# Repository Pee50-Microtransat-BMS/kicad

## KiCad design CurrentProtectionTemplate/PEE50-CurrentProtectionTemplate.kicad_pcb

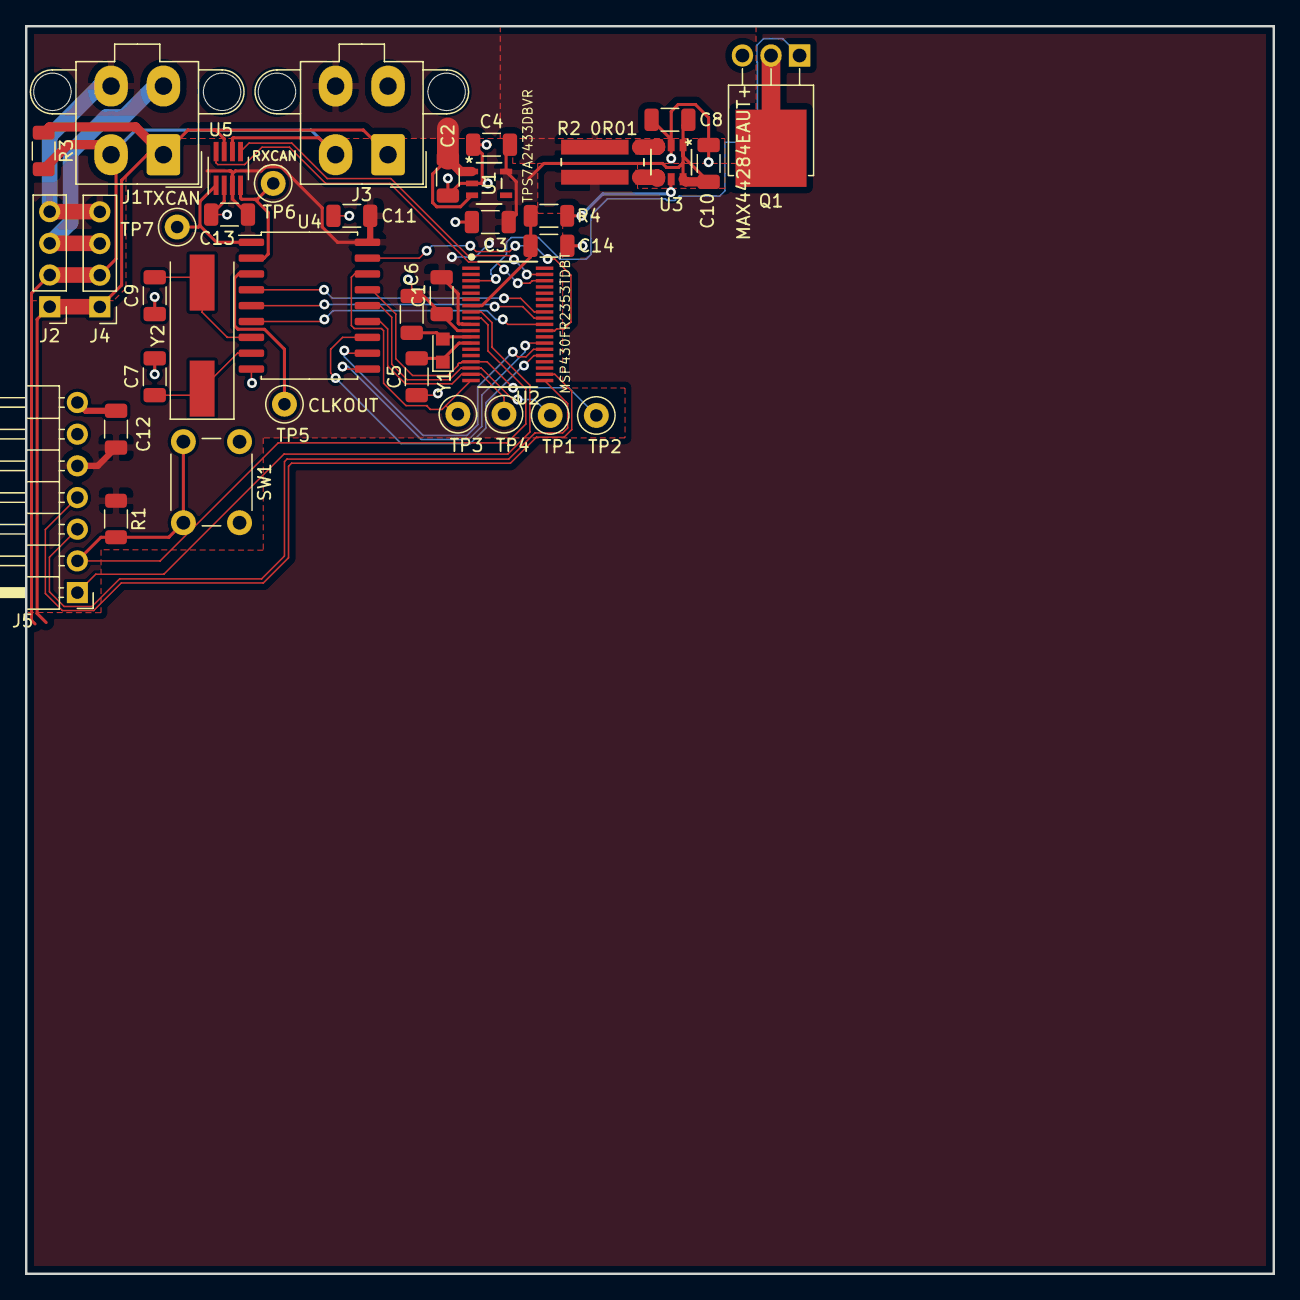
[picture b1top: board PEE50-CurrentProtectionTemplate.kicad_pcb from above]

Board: 2 copper layers, 100.0 x 100.0 mm, 39 parts (0 on the bottom side), 35 nets.

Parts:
C1, C4, C8, C11, C12, C13: 100nF; C_1206_3216Metric
C2: 1uF; C_1206_3216Metric
C3, C10: 4.7uF; C_1206_3216Metric
C5, C6: 12pF; C_1206_3216Metric
C7, C9: 18pF; C_1206_3216Metric
C14: 22nF; C_1206_3216Metric
J1: CAN_IN; Molex_Mini-Fit_Jr_5566-04A2_2x02_P4.20mm_Vertical
J2: CAN_IN; PinHeader_1x04_P2.54mm_Vertical
J3: CAN_OUT; Molex_Mini-Fit_Jr_5566-04A2_2x02_P4.20mm_Vertical
J4: CAN_OUT; PinHeader_1x04_P2.54mm_Vertical
J5: Launchpad_Programming; PinHeader_1x07_P2.54mm_Horizontal
Q1: RFD14N05L; TO-251-3-1EP_Horizontal_TabDown
R1: 47k; R_1206_3216Metric
R2: 0R01; FC4L64R010FER
R3: DNP; R_1206_3216Metric
R4: 1.8k; R_1206_3216Metric
SW1: SW_Push; SW_PUSH_6mm
TP1: SPI_SlaveIn; TestPoint_Loop_D1.80mm_Drill1.0mm_Beaded
TP2: SPI_SlaveOut; TestPoint_Loop_D1.80mm_Drill1.0mm_Beaded
TP3: SPI_ChipSel; TestPoint_Loop_D1.80mm_Drill1.0mm_Beaded
TP4: SPI_SysClk; TestPoint_Loop_D1.80mm_Drill1.0mm_Beaded
TP5: CLKOUT; TestPoint_Loop_D1.80mm_Drill1.0mm_Beaded
TP6: RXCAN; TestPoint_Loop_D1.80mm_Drill1.0mm_Beaded
TP7: TXCAN; TestPoint_Loop_D1.80mm_Drill1.0mm_Beaded
U1: TPS7A2433DBVR; TPS7A2401DBVR
U2: MSP430FR2353TDBT
U3: MAX44284EAUT+; MAX44284EAUT&plus_
U4: MCP2515-xSO; SOIC-18W_7.5x11.6mm_P1.27mm
U5: MAX3051; SOT-23-8_Handsoldering
Y1: 32.768kHz; Crystal_SMD_2012-2Pin_2.0x1.2mm_HandSoldering
Y2: 4.0MHz; Crystal_SMD_HC49-SD

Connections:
+3V3: C1.2, C3.1, C4.2, C8.1, C10.1, C11.2, C12.2, C13.1, J5.5, R1.1, U1.5, U2.10, U3.1, U3.6, U4.18, U5.3
+12V: C2.2, J1.4, J2.4, J3.4, J4.4, R2.1, U1.1, U1.3
/Beveiliging/CANH: J1.1, J2.1, J3.1, J4.1, R3.1, U5.7
/Beveiliging/CANL: J1.2, J2.2, J3.2, J4.2, R3.2, U5.6
/Beveiliging/OSC1: C7.1, U4.8, Y2.1
/Beveiliging/OSC2: C9.2, U4.7, Y2.2
/Beveiliging/RS_STBY_CAN: U2.36, U5.8
/Beveiliging/RXD: J5.4, U2.21
/Beveiliging/SBWTCK: J5.1, U2.8
/Beveiliging/SBWTDIO: J5.2, R1.2, SW1.2, U2.9
/Beveiliging/SHDN_CAN: U2.37, U5.5
/Beveiliging/SlaveIn: TP1.1, U2.17, U4.14
/Beveiliging/SlaveOut: TP2.1, U2.16, U4.15
/Beveiliging/SysClk: TP4.1, U2.18, U4.13
/Beveiliging/TXD: J5.3, U2.20
/Beveiliging/Vcurrent: C14.1, R4.1, U2.7
/Beveiliging/XIN: C6.1, U2.12, Y1.2
/Beveiliging/XOUT: C5.1, U2.13, Y1.1
/Beveiliging/~ChipSel: TP3.1, U2.19, U4.16
/Beveiliging/~ENABLE: Q1.1, U2.3
/Beveiliging/~INT: U2.24, U4.12
/Beveiliging/~RST_CAN: U2.28, U4.17
/Beveiliging/~RX0INT: U2.25, U4.11
/Beveiliging/~RX1INT: U2.26, U4.10
/Beveiliging/~TX0RTS: U2.31, U4.4
/Beveiliging/~TX1RTS: U2.30, U4.5
/Beveiliging/~TX2RTS: U2.29, U4.6
GND: Q1.2, Q1.4
GNDPWR: C1.1, C2.1, C3.2, C4.1, C5.2, C6.2, C7.2, C8.2, C9.1, C10.2, C11.1, C12.1, C13.2, C14.2, J1.3, J2.3, J3.3, J4.3, J5.7, Q1.3, SW1.1, U1.2, U2.11, U3.2, U4.9, U5.2
unnamed: R2.2, U3.3
unnamed: R2.3, U3.4
unnamed: R4.2, U3.5
unnamed: TP5.1, U4.3
unnamed: TP6.1, U4.2, U5.4
unnamed: TP7.1, U4.1, U5.1

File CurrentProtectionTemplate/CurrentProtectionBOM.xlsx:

Item | Qty | Reference(s) | Value | LibPart | Footprint | Vendor Website |  | Datasheet | Comment | Decoupling | Manufacturer
1 | 6 | C1, C4, C8, C11, C12, C13 | 100nF | Device:C | Capacitor_SMD:C_1206_3216Metric | ~ |  |  |  | MSP430
2 | 1 | C2 | 1uF | Device:C_Small | Capacitor_SMD:C_1206_3216Metric | ~
3 | 1 | C3 | 4.7uF | Device:C_Small | Capacitor_SMD:C_1206_3216Metric | ~
5 | 2 | C5, C6 | 12pF | Device:C_Small | Capacitor_SMD:C_1206_3216Metric | ~
6 | 2 | C7, C9 | 18pF | Device:C_Small | Capacitor_SMD:C_1206_3216Metric | ~
7 | 1 | C10 | 4.7uF | Device:C | Capacitor_SMD:C_1206_3216Metric | ~ |  |  |  | MAX44284
8 | 1 | C14 | 22nF | Device:C | Capacitor_SMD:C_1206_3216Metric | ~
9 | 4 | J1 | CAN_IN | Connector:Conn_01x04_Female | Connector_Molex:Molex_Mini-Fit_Jr_5566-04A2_2x02_P4.20mm_Vertical | https://nl.farnell.com/molex/39-29-9043/connector-header-4po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 | 1756683
13 | 1 | J5 | Launchpad_Programming | msp430fr2353tdbt:Launchpad_Interface | Connector_PinHeader_2.54mm:PinHeader_1x07_P2.54mm_Horizontal | https://nl.farnell.com/samtec/ssw-107-02-g-s-ra/receptacle-2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 | 1668361
14 | 1 | Q1 | RFD14N05L | Device:Q_NMOS_GDSD | Package_TO_SOT_THT:TO-251-3-1EP_Horizontal_TabDown | https://nl.farnell.com/on-semiconductor/rfd14n05l/mosfet-n-l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 | 1017789
15 | 1 | R1 | 47k | Device:R | Resistor_SMD:R_1206_3216Metric | ~
16 | 1 | R2 | 0R01 | Device:R_Shunt | footprints:FC4L64R010FER |  |  | https://docs.rs-online.com/1f7c/0900766b815640ef.pdf |  |  | FC4L64R010FER
17 | 1 | R3 | DNP | Device:R_Small | Resistor_SMD:R_1206_3216Metric | ~ |  |  | Only place on ends of the bus (120R)
18 | 1 | R4 | 1.8k | Device:R | Resistor_SMD:R_1206_3216Metric | ~
19 | 1 | R5 | LOAD | Device:R | Connector_Wire:SolderWire-1.5sqmm_1x02_P6mm_D1.7mm_OD3mm_Relief | https://nl.farnell.com/arcol/hs100-2r5-f/resistor-wirewound-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 | 2678726
20 | 1 | SW1 | SW_Push | Switch:SW_Push | Button_Switch_THT:SW_PUSH_6mm | https://nl.farnell.com/c-k-components/pts645sl50-2-lfs/tacti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 | 2435162
21 | 1 | U1 | TPS7A2433DBVR | 2021-04-28_09-49-34:TPS7A2433DBVR | footprints:TPS7A2401DBVR | https://www.ti.com/store/ti/en/p/product/?p=TPS7A2433DBVR | TPS7A2433DBVR | https://www.ti.com/lit/ds/symlink/tps7a24.pdf
22 | 1 | U2 | MSP430FR2353TDBT | msp430fr2353tdbt:MSP430FR2353TDBT | footprints:MSP430FR2353TDBT | https://www.digikey.com/en/products/detail/texas-instruments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 | 296-53253-ND | https://www.ti.com/lit/ds/symlink/msp430fr2353.pdf
23 | 1 | U3 | MAX44284EAUT+ | 2021-04-28_08-31-09:MAX44284EAUT+ | footprints:MAX44284EAUT&plus_ | https://nl.farnell.com/maxim-integrated-products/max44284eau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 | 2909815 | https://datasheets.maximintegrated.com/en/ds/MAX44284.pdf
24 | 1 | U4 | MCP2515-xSO | Interface_CAN_LIN:MCP2515-xSO | Package_SO:SOIC-18W_7.5x11.6mm_P1.27mm | https://nl.farnell.com/microchip/mcp2515-e-so/can-controller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 | 1605565 | https://ww1.microchip.com/downloads/en/DeviceDoc/MCP2515-Sta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
25 | 1 | U5 | MAX3051 | Interface_UART:MAX3051 | Package_TO_SOT_SMD:SOT-23-8_Handsoldering | https://nl.farnell.com/maxim-integrated-products/max3051eka-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 | 2517387 | http://datasheets.maximintegrated.com/en/ds/MAX3051.pdf
26 | 1 | Y1 | 32.768kHz | Device:Crystal_Small | Crystal:Crystal_SMD_2012-2Pin_2.0x1.2mm_HandSoldering | https://nl.farnell.com/abracon/abs06-32-768khz-1-t/crystal-3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 | 2101344
27 | 1 | Y2 | 4.0MHz | Device:Crystal_Small | Crystal:Crystal_SMD_HC49-SD | https://nl.farnell.com/abracon/abls-4-000mhz-k4t/crystal-4mh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 | 2467753

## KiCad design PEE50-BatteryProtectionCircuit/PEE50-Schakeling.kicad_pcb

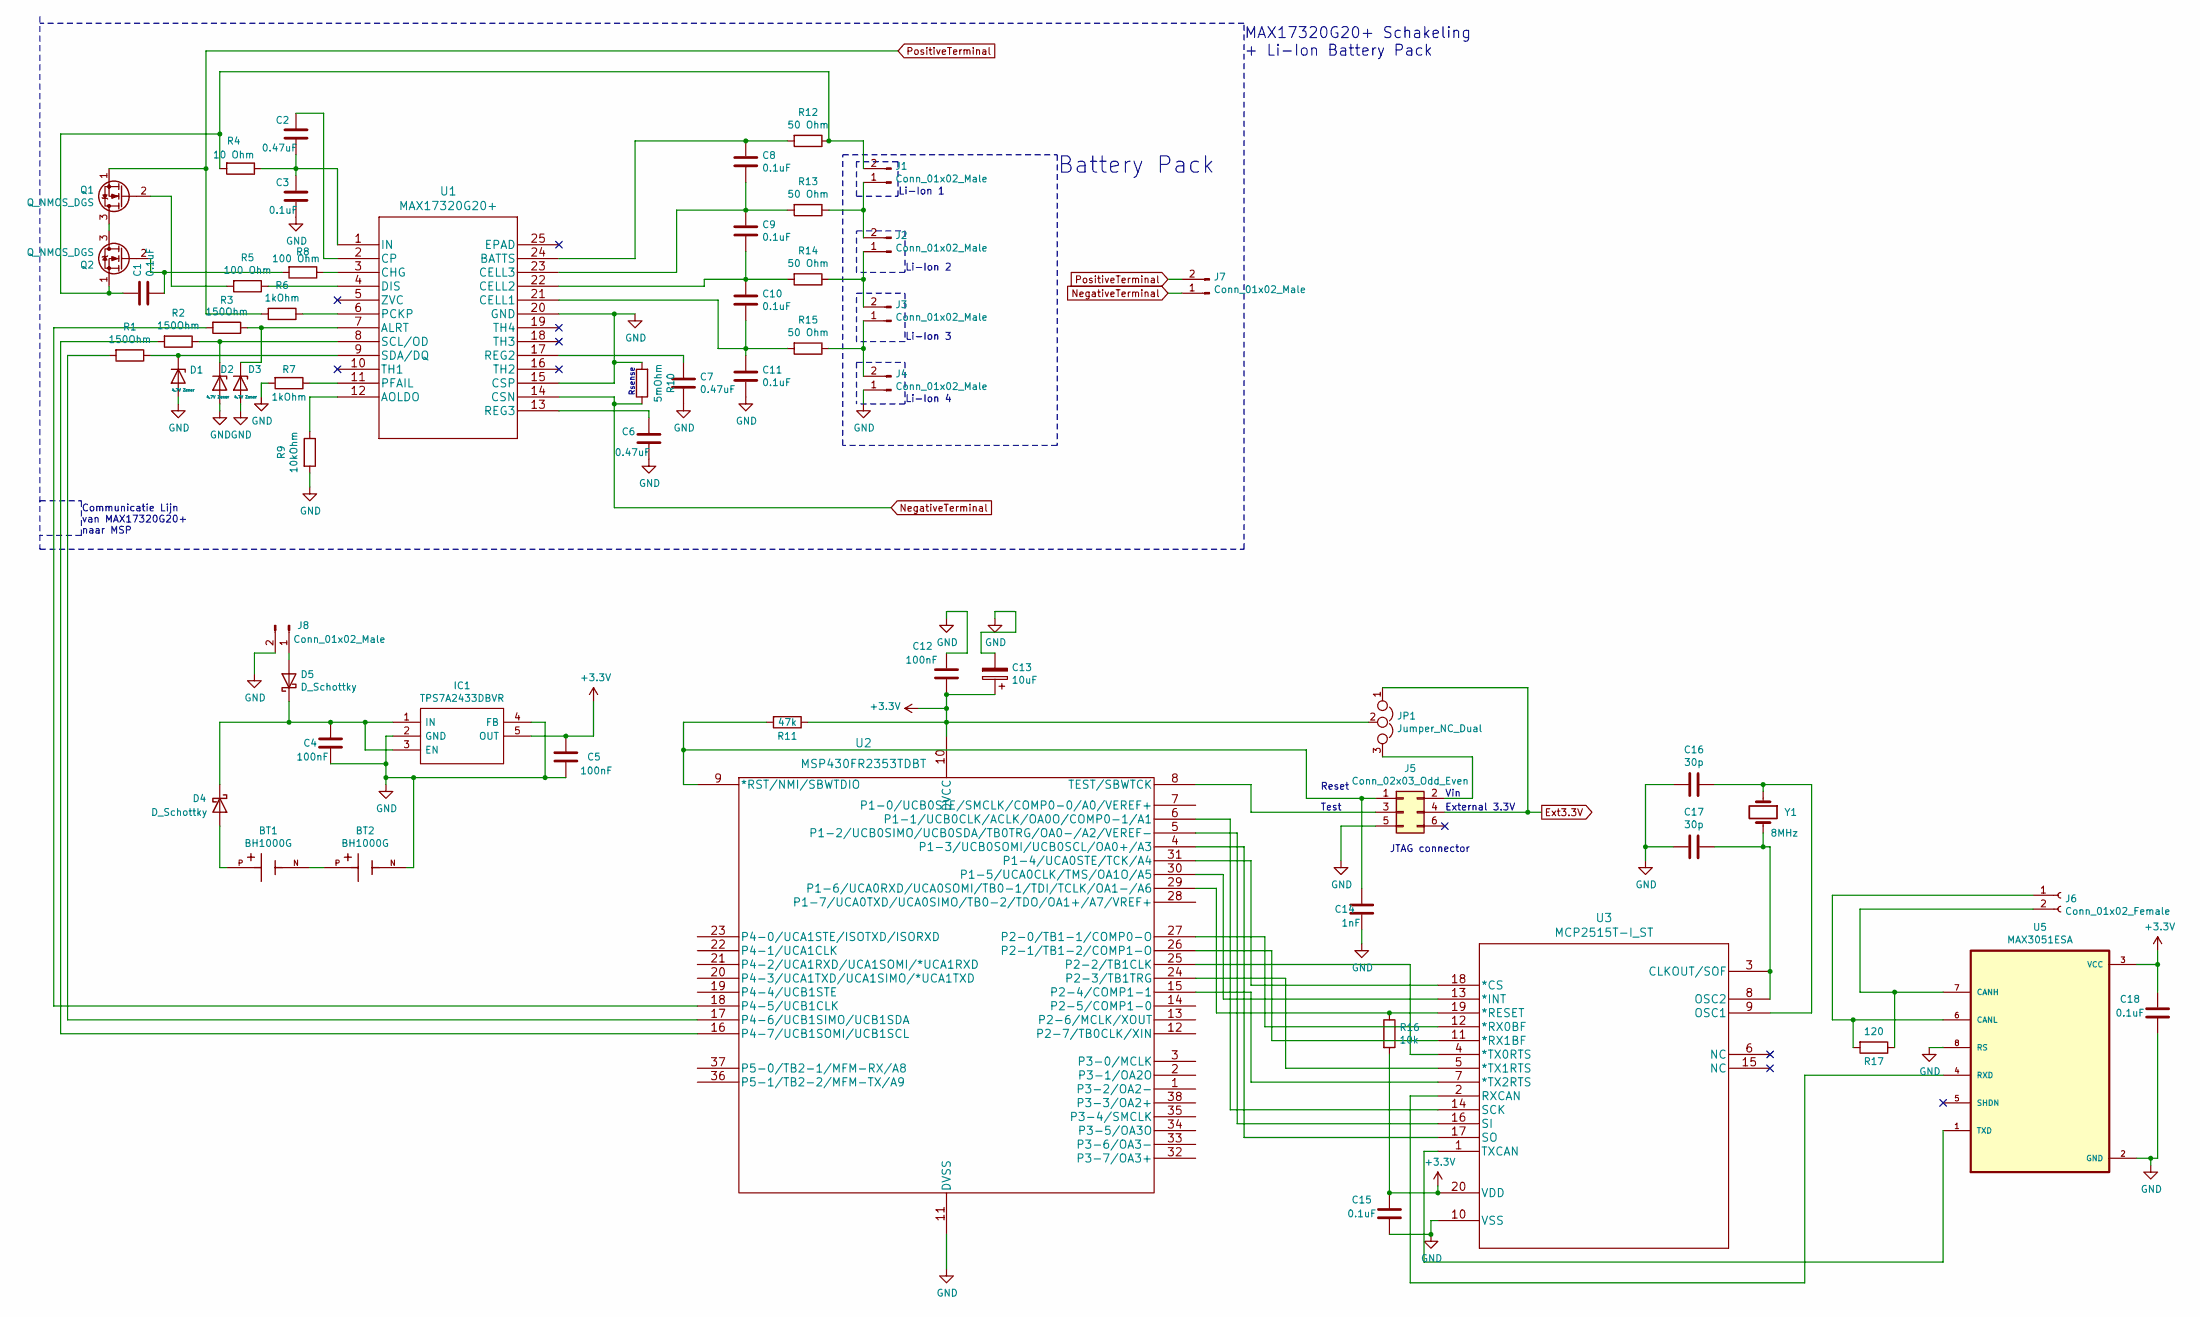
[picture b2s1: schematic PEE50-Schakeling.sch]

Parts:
BT1, BT2: BH1000G; BAT_BH1000G; PARTREV E
C1, C3, C8, C9, C10, C11, C15, C18: 0.1uF; C_0603_1608Metric
C2, C6, C7: 0.47uF; C_0603_1608Metric
C4, C5, C12: 100nF; C_0603_1608Metric
C13: 10uF; C_0603_1608Metric
C14: 1nF; C_0603_1608Metric
C16, C17: 30p; C_0603_1608Metric
D1, D2, D3: 4.7V Zener; D_0603_1608Metric_Castellated
D4, D5: D_Schottky; D_0603_1608Metric
IC1: TPS7A2433DBVR; SOT95P280X145-5N; Manufacturer_Part_Number TPS7A2433DBVR; Mouser Part Number 595-TPS7A2433DBVR
J1, J2, J3, J4, J7, J8: Conn_01x02_Male; PhoenixContact_MSTBA_2,5_2-G-5,08_1x02_P5.08mm_Horizontal
J5: Conn_02x03_Odd_Even; PinHeader_2x03_P2.54mm_Vertical
J6: Conn_01x02_Female; Molex_Mini-Fit_Jr_5566-04A2_2x02_P4.20mm_Vertical
JP1: Jumper_NC_Dual; PinHeader_1x03_P2.54mm_Vertical
Q1, Q2: Q_NMOS_DGS; VSONP-8-1EP_5x6_P1.27mm
R1, R2, R3: 150Ohm; R_0603_1608Metric
R4: 10 Ohm; R_0603_1608Metric
R5, R8: 100 Ohm; R_0603_1608Metric
R6, R7: 1kOhm; R_0603_1608Metric
R9: 10kOhm; R_0603_1608Metric
R10: 5mOhm; R_0603_1608Metric
R11: 47k; R_0603_1608Metric
R12, R13, R14, R15: 50 Ohm; R_0603_1608Metric
R16: 10k; R_0603_1608Metric
R17: 120; R_0603_1608Metric
U1: MAX17320G20+; MAX17320G20&plus_
U2: MSP430FR2353TDBT
U3: MCP2515T-I_ST; MCP2515T-I&slash_ST
U5: MAX3051ESA; SOIC127P600X175-8N
Y1: 8MHz; Crystal_HC49-4H_Vertical

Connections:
+3V3: C5.2, C12.1, C13.1, C15.2, C18.2, IC1.5 (OUT), JP1.2, R11.1, R16.2, U2.10 (DVCC), U3.20 (VDD), U5.3 (VCC)
Ext3.3V: J5.4, JP1.1
GND: BT2.N, C3.2, C4.1, C5.1, C6.2, C7.2, C11.2, C12.2, C13.2, C14.1, C15.1, C16.2, C17.2, C18.1, D1.2 (A), D2.2 (A), D3.2 (A), IC1.2 (GND), IC1.4 (FB), J4.1, J5.5, J8.2, R7.2, R9.2, R10.2, U1.15 (CSP), U1.20 (GND), U2.11 (DVSS), U3.10 (VSS), U5.2 (GND), U5.8 (RS)
NegativeTerminal: J7.1, R10.1, U1.14 (CSN)
unnamed: BT1.N, BT2.P
unnamed: BT1.P, D4.2 (A)
unnamed: C1.1, J1.2, Q2.1 (S), R4.2, R12.1
unnamed: C1.2, Q2.2 (G), R8.2
unnamed: C2.1, U1.2 (CP)
unnamed: C2.2, C3.1, R4.1, U1.1 (IN)
unnamed: C4.2, D4.1 (K), D5.1 (K), IC1.1 (IN), IC1.3 (EN)
unnamed: C6.1, U1.13 (REG3)
unnamed: C7.1, U1.17 (REG2)
unnamed: C8.1, R12.2, U1.24 (BATTS)
unnamed: C8.2, C9.1, R13.2, U1.23 (CELL3)
unnamed: C9.2, C10.1, R14.2, U1.22 (CELL2)
unnamed: C10.2, C11.1, R15.2, U1.21 (CELL1)
unnamed: C14.2, J5.1, R11.2, U2.9 (*RST/NMI/SBWTDIO)
unnamed: C16.1, U3.9 (OSC1), Y1.1
unnamed: C17.1, U3.3 (CLKOUT/SOF), U3.8 (OSC2), Y1.2
unnamed: D1.1 (K), R1.1, U1.9 (SDA/DQ)
unnamed: D2.1 (K), R2.1, U1.8 (SCL/OD)
unnamed: D3.1 (K), R3.1, U1.7 (ALRT)
unnamed: D5.2 (A), J8.1
unnamed: J1.1, J2.2, R13.1
unnamed: J2.1, J3.2, R14.1
unnamed: J3.1, J4.2, R15.1
unnamed: J5.2, JP1.3
unnamed: J5.3, U2.8 (TEST/SBWTCK)
unnamed: J6.1, R17.2, U5.6 (CANL)
unnamed: J6.2, R17.1, U5.7 (CANH)
unnamed: Q1.2 (G), R5.2
unnamed: Q1.3 (D), Q2.3 (D)
unnamed: R1.2, U2.17 (P4-6/UCB1SIMO/UCB1SDA)
unnamed: R2.2, U2.16 (P4-7/UCB1SOMI/UCB1SCL)
unnamed: R3.2, U2.18 (P4-5/UCB1CLK)
unnamed: R5.1, U1.4 (DIS)
unnamed: R6.1, U1.6 (PCKP)
unnamed: R7.1, U1.11 (PFAIL)
unnamed: R8.1, U1.3 (CHG)
unnamed: R9.1, U1.12 (AOLDO)
unnamed: R16.1, U2.29 (P1-6/UCA0RXD/UCA0SOMI/TB0-1/TDI/TCLK/OA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), U3.19 (*RESET)
unnamed: U2.4 (P1-3/UCB0SOMI/UCB0SCL/OA0+/A3), U3.17 (SO)
unnamed: U2.5 (P1-2/UCB0SIMO/UCB0SDA/TB0TRG/OA0-/A2/VE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), U3.16 (SI)
unnamed: U2.6 (P1-1/UCB0CLK/ACLK/OA0O/COMP0-1/A1), U3.14 (SCK)
unnamed: U2.15 (P2-4/COMP1-1), U3.7 (*TX2RTS)
unnamed: U2.24 (P2-3/TB1TRG), U3.5 (*TX1RTS)
unnamed: U2.25 (P2-2/TB1CLK), U3.4 (*TX0RTS)
unnamed: U2.26 (P2-1/TB1-2/COMP1-O), U3.11 (*RX1BF)
unnamed: U2.27 (P2-0/TB1-1/COMP0-O), U3.12 (*RX0BF)
unnamed: U2.30 (P1-5/UCA0CLK/TMS/OA1O/A5), U3.13 (*INT)
unnamed: U2.31 (P1-4/UCA0STE/TCK/A4), U3.18 (*CS)
unnamed: U3.1 (TXCAN), U5.1 (TXD)
unnamed: U3.2 (RXCAN), U5.4 (RXD)
PositiveTerminal: J7.2, Q1.1 (S), R6.2

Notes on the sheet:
Communicatie Lijn van MAX17320G20+ naar MSP
Battery Pack
Li-Ion 1
Li-Ion 2
Li-Ion 3
Li-Ion 4
MAX17320G20+ Schakeling + Li-Ion Battery Pack
Rsense
JTAG connector
Reset
Test
Vin
External 3.3V

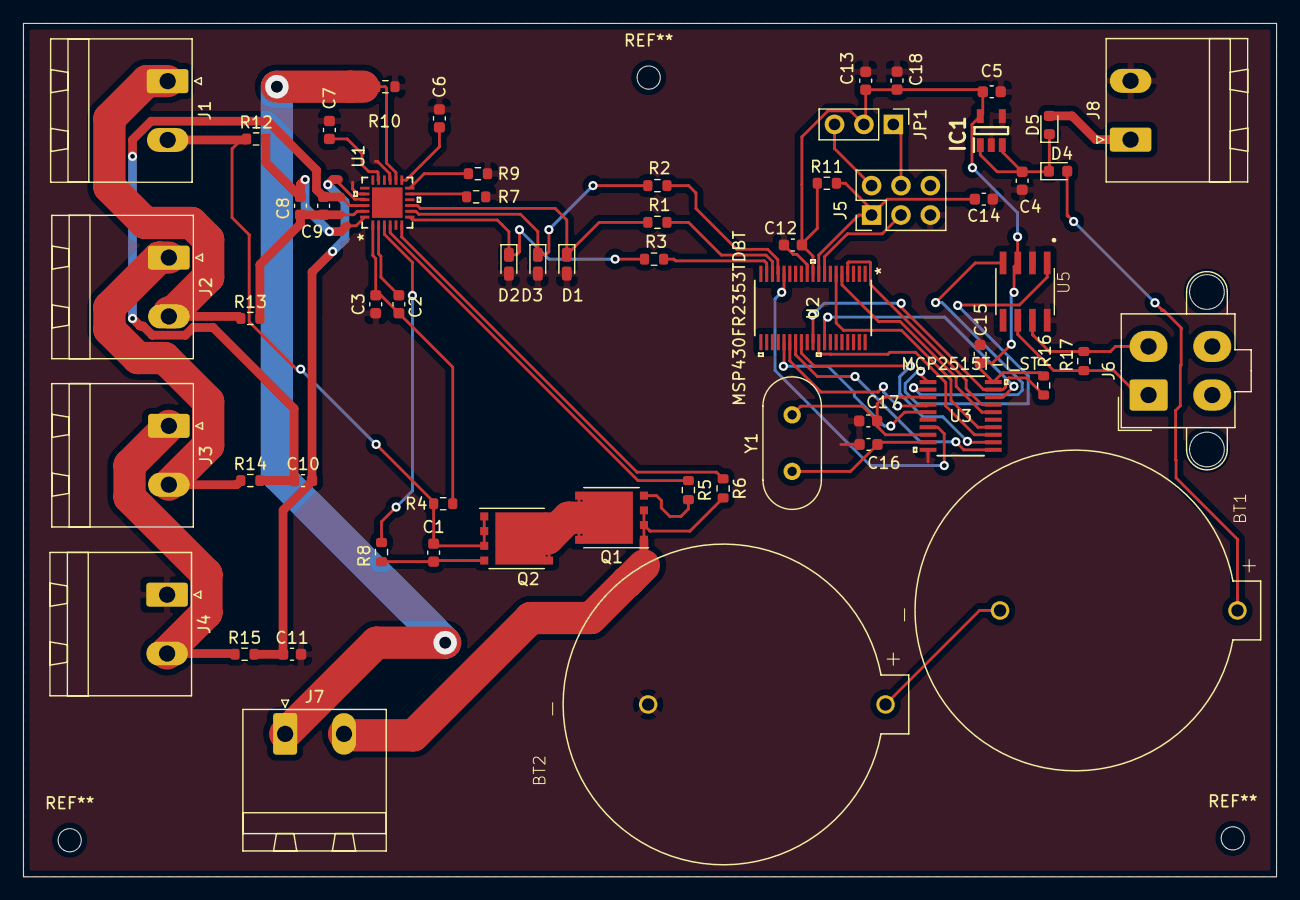
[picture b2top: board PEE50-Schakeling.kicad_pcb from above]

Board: 2 copper layers, 108.2 x 73.7 mm, 59 parts (0 on the bottom side), 55 nets.

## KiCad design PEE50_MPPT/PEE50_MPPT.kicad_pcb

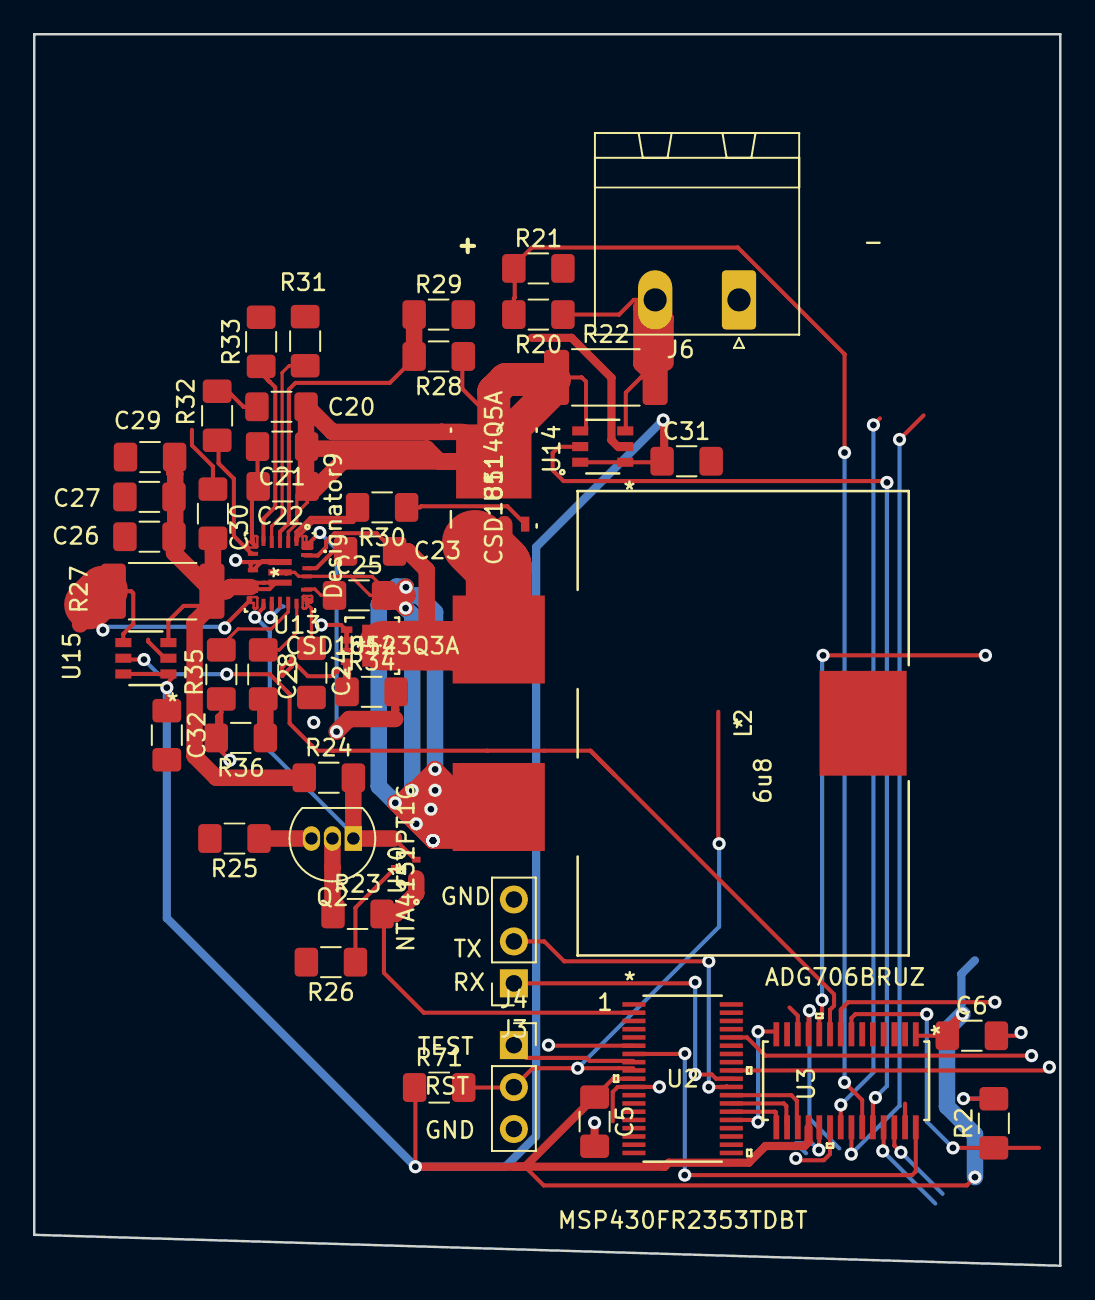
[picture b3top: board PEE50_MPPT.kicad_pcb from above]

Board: 2 copper layers, 62.2 x 74.6 mm, 47 parts (0 on the bottom side), 40 nets.

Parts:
C5: C; C_1206_3216Metric_Pad1.42x1.75mm_HandSolder
C6, C23, C25, C28, C31, C32: 100n; C_1206_3216Metric_Pad1.42x1.75mm_HandSolder
C20, C21: 150u; C_1206_3216Metric_Pad1.42x1.75mm_HandSolder
C22, C26, C27: 10u; C_1206_3216Metric_Pad1.42x1.75mm_HandSolder
C24: 4u7; C_1206_3216Metric_Pad1.42x1.75mm_HandSolder
C29, C30: 39u; C_1206_3216Metric_Pad1.42x1.75mm_HandSolder
J3, J4: Conn_01x03_Female; PinSocket_1x03_P2.54mm_Vertical
J6: PV_IN1; PhoenixContact_MSTBA_2,5_2-G-5,08_1x02_P5.08mm_Horizontal
L2: 6u8; SER2915L-153KL
Q2: BC547; TO-92_Inline
R2, R21: 20k; R_1206_3216Metric_Pad1.42x1.75mm_HandSolder
R20: 180k; R_1206_3216Metric_Pad1.42x1.75mm_HandSolder
R22, R27: 0.01; R_2512_6332Metric_Pad1.52x3.35mm_HandSolder
R23, R25, R26: R; R_1206_3216Metric_Pad1.42x1.75mm_HandSolder
R24, R71: 10k; R_1206_3216Metric_Pad1.42x1.75mm_HandSolder
R28: 383k; R_1206_3216Metric_Pad1.42x1.75mm_HandSolder
R29, R31, R33: 100k; R_1206_3216Metric_Pad1.42x1.75mm_HandSolder
R30, R34: 1; R_1206_3216Metric_Pad1.42x1.75mm_HandSolder
R32: 66.5k; R_1206_3216Metric_Pad1.42x1.75mm_HandSolder
R35: 21k; R_1206_3216Metric_Pad1.42x1.75mm_HandSolder
R36: 13k; R_1206_3216Metric_Pad1.42x1.75mm_HandSolder
U2: MSP430FR2353TDBT; DBT38_TEX
U3: ADG706BRUZ
U10: NTA4151PT1G
U11: CSD18514Q5A; DQJ0008A
U12: CSD18543Q3A; DNH0008A
U13: TPS552882QRPMRQ1; RPM0026A-MFG
U14, U15: MAX44284FAUT+T; 21-0058I_MXM

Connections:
+3V3: C5.1, C6.1, C31.1, C32.1, R71.1, U2.10, U3.1, U3.18, U14.1, U14.6, U15.1, U15.6
/Sheet609B465C/Vout: R27.1, U13.13, U15.4
/mux/A0: U2.27, U3.17
/mux/A1: U2.26, U3.16
/mux/A2: U2.25, U3.15
/mux/A3: U2.24, U3.14
/sheet609F26BA/sheet609C6964/FB: Q2.1, R24.2, U10.2, U13.14
/sheet609F26BA/sheet609C6964/ISP: C26.1, C27.1, C29.1, C30.1, R24.1, R27.2, U13.11, U13.12, U13.26, U15.3
/sheet609F26BA/sheet609C6964/PVin+: C20.1, C21.1, C22.1, R22.1, R28.1, U11.5, U11.6, U11.7, U11.8, U11.9, U13.3, U14.4
/sheet609F26BA/sheet609C6965/R+: J6.2, R20.1, R22.2, U14.3
/uC_MPPT/ADC: U2.7, U3.28
DAC3: R23.2, U2.2, U10.1
Imppt3: U3.9, U15.5
Ipv3: U3.24, U14.5
unnamed: C23.1, L2.1, U11.1, U11.2, U11.3, U12.5, U12.6, U12.7, U12.8, U12.9, U13.23
unnamed: C23.2, U13.22
unnamed: C24.1, U13.19
unnamed: C25.1, U13.20
unnamed: C25.2, L2.2, U13.21, U13.25
unnamed: C28.1, R36.1
unnamed: C28.2, U13.18
unnamed: J3.1, U2.29
unnamed: J3.2, U2.28
unnamed: J4.1, U2.8
unnamed: J4.2, R71.2, U2.9
unnamed: Q2.2, R23.1
unnamed: Q2.3, R25.1
unnamed: R26.1, U10.3
unnamed: R28.2, R29.1, U13.4
unnamed: R30.1, U11.4
unnamed: R30.2, U13.2
unnamed: R31.1, U13.5
unnamed: R32.1, U13.8
unnamed: R33.1, U13.6
unnamed: R34.1, U12.4
unnamed: R34.2, U13.1
unnamed: R35.1, U13.17
Pgnd: C5.2, C6.2, C20.2, C21.2, C22.2, C24.2, C26.2, C27.2, C29.2, C30.2, C31.2, C32.2, J3.3, J4.3, J6.1, R2.2, R21.2, R25.2, R26.2, R29.2, R31.2, R32.2, R33.2, R35.2, R36.2, U2.11, U3.12, U3.27, U12.1, U12.2, U12.3, U13.7, U13.9, U13.10, U13.15, U13.24, U14.2, U15.2
Vout: R2.1, U3.7
Vpv3: R20.2, R21.1, U3.23

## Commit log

2021-03-01 FUCK YOU SOURCETREE
2021-03-01 Test commit Mounir
2021-03-01 Niet van Björn maar misschien wel van mij
2021-04-27 buck/boost aangemaakt (beginnetje)
2021-04-28 redelijk ver met de DC/DC schakeling overnemen
2021-04-28 Cleanup
2021-04-28 Should not commit -fp-cache files, if doing footprints correctly.
2021-04-28 First version
2021-04-30 microcontroller ingevoegd, current sense ingevoegd
2021-04-30 copy + pasten van schakeling
2021-04-30 mux ingevoegd en geintegreerd
2021-04-30 meetsignalen doorgevoerd naar mux
2021-04-30 laatste spanning bijgevoegd (was vergeten)
2021-04-30 verschil gemaakt tussen Agnd en Pgnd
2021-04-30 toch maar wel Pgnd en Agnd verbonden met ontkoppel C
2021-05-04 schakeling klaar (denk ik)
2021-05-04 weerstand waardes ingevoegd
2021-05-05 Main branch deed vaag, kon daardoor alle branches niet zien maar wel mergen met main. Heb alle branches gemerged met de main waardoor ik weer bij ze kon. Negeer maar wat er op dit moment in main staa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
2021-05-05 ignore.txt weer deleted
2021-05-05 De KiCad schakeling van het battery protection circuit / state of charge bijhouden. Deze branch wordt later nog gemerged met Mounir zijn branch wanneer beide schakeling worden gecombineerd op 1 .sch 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
2021-05-06 best veel footprints ingevoegd
2021-05-06 footprints gemapt + 10x10 pcb rand getekend
2021-05-06 eerste MPPT gelay-out + een aantal sporen gelegd
2021-05-06 Vorige versie was outdated doordat of ik of kicad niet fatsoenlijk op ctrl+s kan klikken :) Nu wel de meest recente versie
2021-05-06 CAN schema toegevoegd voor deel. Faissal en Mounir schema's gecombineerd.
2021-05-08 push
2021-05-08 best veel al gedaan voor 1e mppt
2021-05-08 1e MPPT lijkt af, nou maar hopen dat copy + paste werkt
2021-05-11 maar opnieuw begonnen met mppt layouten ivm plugin regels
2021-05-11 1e mppt klaar (nog een keer)
2021-05-11 Schakeling updated met nieuwe transceiver
2021-05-11 Microcontroller connected. TODO: Disconnect client.
2021-05-11 Pinout FETs verwisseld
2021-05-11 4 mppt's klaar en geplaatst
2021-05-11 Een aantal footprints gekozen
2021-05-12 power banen gerout, locatie toegewezen voor uC
2021-05-12 ik weet niet wat ik heb gedaan, maar; bij deze
2021-05-13 spinneweb aangemaakt
2021-05-13 pff alles verbonden maar veel errors
2021-05-13 gerber gegenereerd om te testen, begonnen aan silkscreen fixen
2021-05-14 PCB begint leven te krijgen
2021-05-15 heel wat silkscreen gefixt
2021-05-15 Routed everything
2021-05-18 reset pin en errors weggewerkt
2021-05-18 reset knop op goede plek neergezet
2021-05-18 PCB gedecimeert
2021-05-18 gerber
2021-05-18 PCB V1.0 finish
2021-05-19 Connector voor 12V toegevoegd aan PCB en schema
2021-05-19 2de coincell batterij holder toegevoegd.
2021-05-19 Paar veranderingen, drill holes toegevoegd en gerber files
2021-05-28 BOM toegevoegd
2021-06-03 Ready for order
2021-06-03 PCB as ordered
2021-06-08 Added High Current Option

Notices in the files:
parts and their libraries:
Copyright 2016 Accelerated Designs. All rights reserved.
